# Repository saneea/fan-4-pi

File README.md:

# fan-4-pi
12V PWM fan for Raspberry Pi

# Problem
Raspberry Pi usually needs cooling fan.
In most cases you may want to use small 5V fan.
I have bought 3 different 5V fans and all of them are too noisy.
On the opposite side it is very easy to buy
regular 12V cooling PWM fan 80x80mm.
So, this project is about using 12V PWM fan for Raspberry Pi.

# Overview 
This project consists of 2 parts
- [software](software)
- [hardware](hardware)

# Software
Software is represented as python script.
It is considered that python [script](software/fan_ctrl/fan_ctrl.py) will be installed
as system [service](software/fan_ctrl/fanctrl.service).
You can [install](software/fan_ctrl/install-service.sh) and [uninstall](software/fan_ctrl/uninstall-service.sh)
the service via shell-scripts.
You may want to tune config file [config.conf](software/fan_ctrl/config.conf).
It contains comments about properties, so it is easy to make it fit to your system.
You can edit it after installation, it lives here `/etc/fan-pwm-control/config.conf`.
After you edit your config file you need to apply it:
```shell
systemctl restart fanctrl.service
```
Do not forget to check your service health
```shell
systemctl status fanctrl.service
```
Also, you can use [print-t.sh](software/fan_ctrl/print-t.sh) and
[print-t-repeat.sh](software/fan_ctrl/print-t-repeat.sh) scripts to know current CPU temperature.

# Hardware
Hardware is just possible electric schemas for connecting your 12V PWM fan to Raspberry Pi.
You can choose any of variants.

## Schema with external power supply (Case A)

### Electric schema

## Schema with internal power supply (Case B)

### Electric schema

### Real device

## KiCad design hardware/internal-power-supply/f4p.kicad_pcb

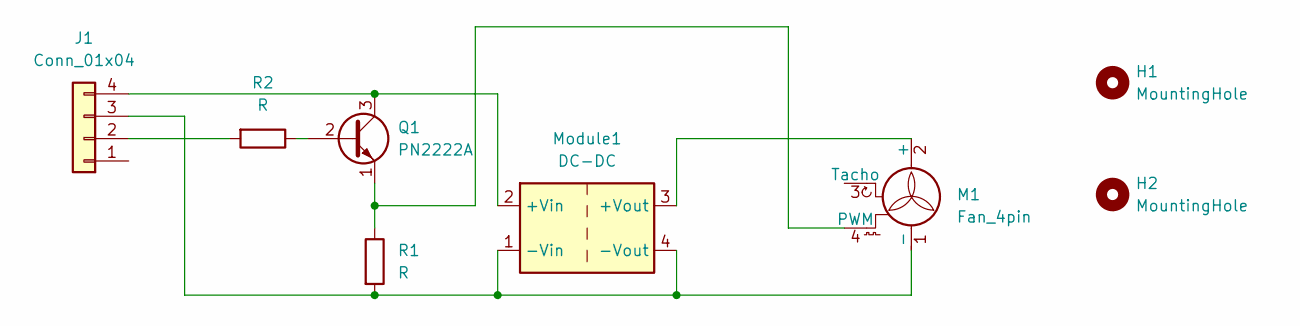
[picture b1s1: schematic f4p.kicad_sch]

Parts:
H1, H2: MountingHole; MountingHole_2mm
J1: Conn_01x04; PinHeader_1x04_P2.54mm_Vertical
M1: Fan_4pin; PinHeader_1x04_P2.54mm_Vertical
Module1: DC-DC; saneea DC-DC
Q1: PN2222A; TO-92_Wide
R1, R2: R; R_Axial_DIN0204_L3.6mm_D1.6mm_P7.62mm_Horizontal

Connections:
unnamed: J1.2, R2.2
unnamed: J1.3, M1.1 (-), Module1.1 (-Vin), Module1.4 (-Vout), R1.2
unnamed: J1.4, Module1.2 (+Vin), Q1.3 (C)
unnamed: M1.2 (+), Module1.3 (+Vout)
unnamed: M1.4 (PWM), Q1.1 (E), R1.1
unnamed: Q1.2 (B), R2.1

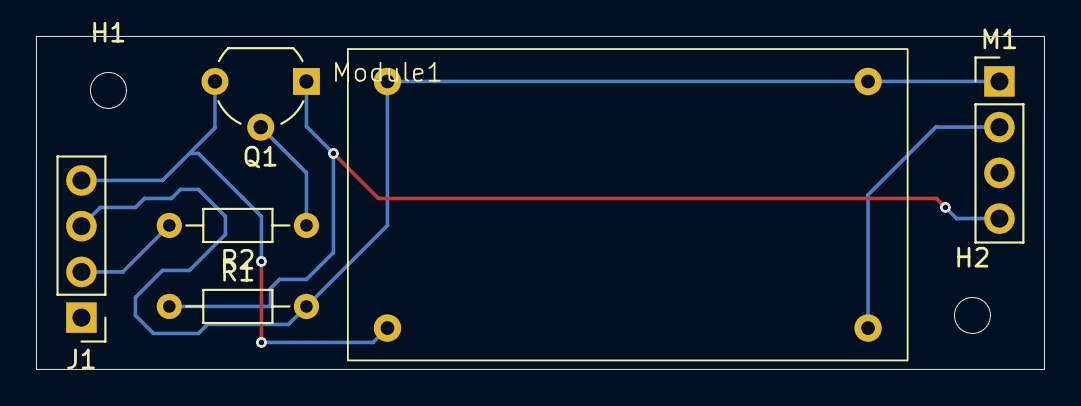
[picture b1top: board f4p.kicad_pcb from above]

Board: 2 copper layers, 56.0 x 18.5 mm, 8 parts (0 on the bottom side), 6 nets.

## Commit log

2021-02-04 add electric schema draft
2021-02-04 add electric schema draft as svg
2024-12-21 add python script with service installer
2024-12-22 logging for systemd
2024-12-22 add script for watch system temperature continuously
2025-02-01 update schema with external power supply
2025-02-01 rename schema files
2025-02-01 move schema files
2025-02-01 add .gitignore
2025-02-01 add kicad schema for internal-power-supply
2025-02-01 add svg representation of schema
2025-02-01 compose readme file
